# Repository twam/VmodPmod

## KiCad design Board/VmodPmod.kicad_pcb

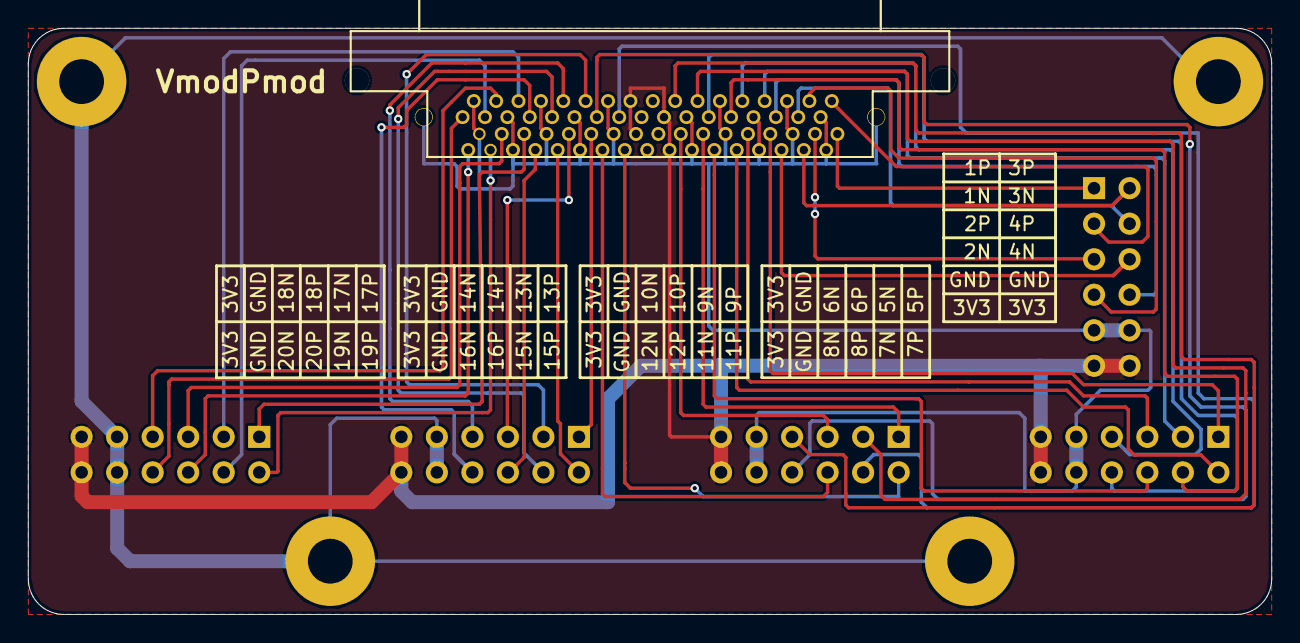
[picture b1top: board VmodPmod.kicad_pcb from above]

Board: 2 copper layers, 88.9 x 41.9 mm, 10 parts (0 on the bottom side), 42 nets.

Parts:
P1, P2, P3, P4, P5: PMOD; PMOD-DUAL-FEMALE
P6: VHDCI
W1, W2, W3, W4: GND; MountingHole_3-2mm_M3_Pad

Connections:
+3V3: P1.6, P1.12, P2.6, P2.12, P3.6, P3.12, P4.6, P4.12, P5.6, P5.12, P6.16, P6.19, P6.50, P6.53
/1N: P1.2, P6.35
/1P: P1.1, P6.1
/2N: P1.4, P6.37
/2P: P1.3, P6.3
/3N: P1.8, P6.38
/3P: P1.7, P6.4
/4N: P1.10, P6.40
/4P: P1.9, P6.6
/5N: P2.2, P6.41
/5P: P2.1, P6.7
/6N: P2.4, P6.43
/6P: P2.3, P6.9
/7N: P2.8, P6.44
/7P: P2.7, P6.10
/8N: P2.10, P6.46
/8P: P2.9, P6.12
/9N: P3.2, P6.47
/9P: P3.1, P6.13
/10N: P3.4, P6.49
/10P: P3.3, P6.15
/11N: P3.8, P6.54
/11P: P3.7, P6.20
/12N: P3.10, P6.56
/12P: P3.9, P6.22
/13N: P4.2, P6.57
/13P: P4.1, P6.23
/14N: P4.4, P6.59
/14P: P4.3, P6.25
/15N: P4.8, P6.60
/15P: P4.7, P6.26
/16N: P4.10, P6.62
/16P: P4.9, P6.28
/17N: P5.2, P6.63
/17P: P5.1, P6.29
/18N: P5.4, P6.65
/18P: P5.3, P6.31
/19N: P5.8, P6.66
/19P: P5.7, P6.32
/20N: P5.10, P6.68
/20P: P5.9, P6.34
GND: P1.5, P1.11, P2.5, P2.11, P3.5, P3.11, P4.5, P4.11, P5.5, P5.11, P6.2, P6.5, P6.8, P6.11, P6.14, P6.21, P6.24, P6.27, P6.30, P6.33, P6.36, P6.39, P6.42, P6.45, P6.48, P6.55, P6.58, P6.61, P6.64, P6.67, P6.S1, P6.S2, W1.1, W2.1, W3.1, W4.1

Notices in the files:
Board/VmodPmod.kicad_pcb:
License: CC-BY-SA 4.0
CC-BY-SA 4.0
